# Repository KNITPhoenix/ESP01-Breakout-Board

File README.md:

# ESP01-Breakout-Board
ESP01 is a module that comes along with ESP8266 and an SPI flash memory but its not breadboard friendly. So in order to program and use it in, we use a breakout development board. This is a simple breakout board that gives the capabilities to program it and use its code simultaneously without much changes.

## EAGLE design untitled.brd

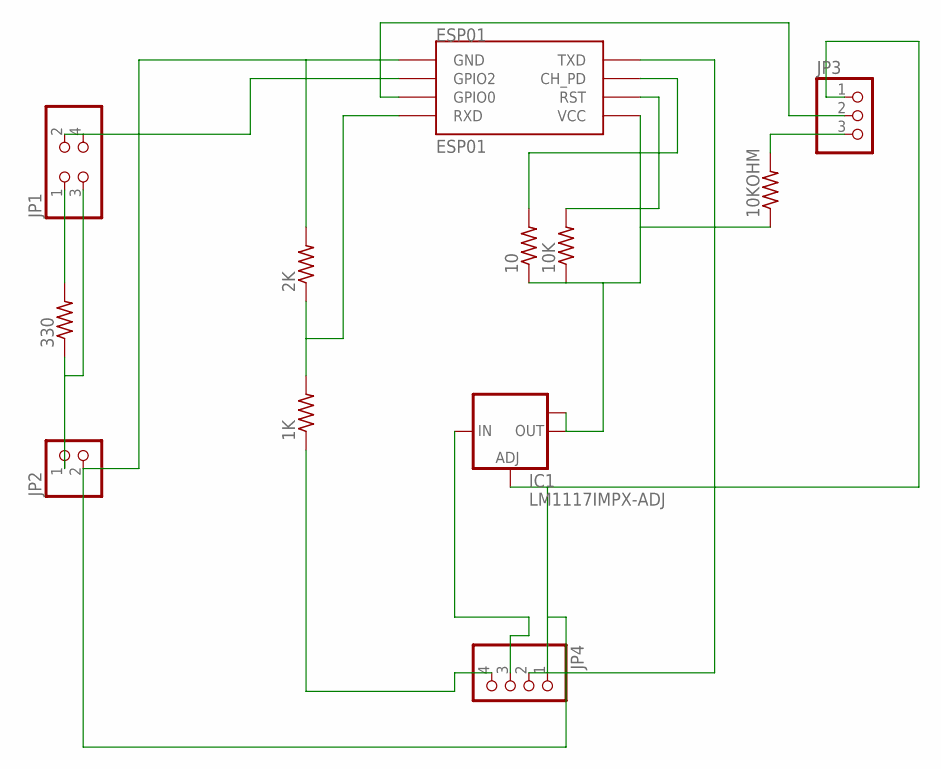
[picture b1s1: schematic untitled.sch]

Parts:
1K, 2K, 10, 10K, 10KOHM, 330: R-US_0204/7; 0204/7
ESP01: ESP01
IC1: LM1117IMPX-ADJ; SOT223
JP1: PINHD-2X2; 2X02
JP2: PINHD-1X2; 1X02
JP3: PINHD-1X3; 1X03
JP4: PINHD-1X4; 1X04

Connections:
unnamed: 330.2, JP1.1
unnamed: 330.1, JP1.3, JP2.1
unnamed: 1K.2, 2K.1, ESP01.RX (RXD)
unnamed: 10.1, 10K.1, 10KOHM.1, ESP01.VCC, IC1.2 (OUT), IC1.TAB (OUT1)
unnamed: 1K.1, JP4.4
unnamed: ESP01.GPIO2, JP1.2, JP1.4
unnamed: 10.2, ESP01.CH_PD
unnamed: 10K.2, ESP01.RST
unnamed: IC1.3 (IN), JP4.3
unnamed: 2K.2, ESP01.GND, IC1.1 (ADJ), JP2.2, JP3.1, JP4.1
unnamed: ESP01.TX (TXD), JP4.2
unnamed: ESP01.GPIO0, JP3.2
unnamed: 10KOHM.2, JP3.3

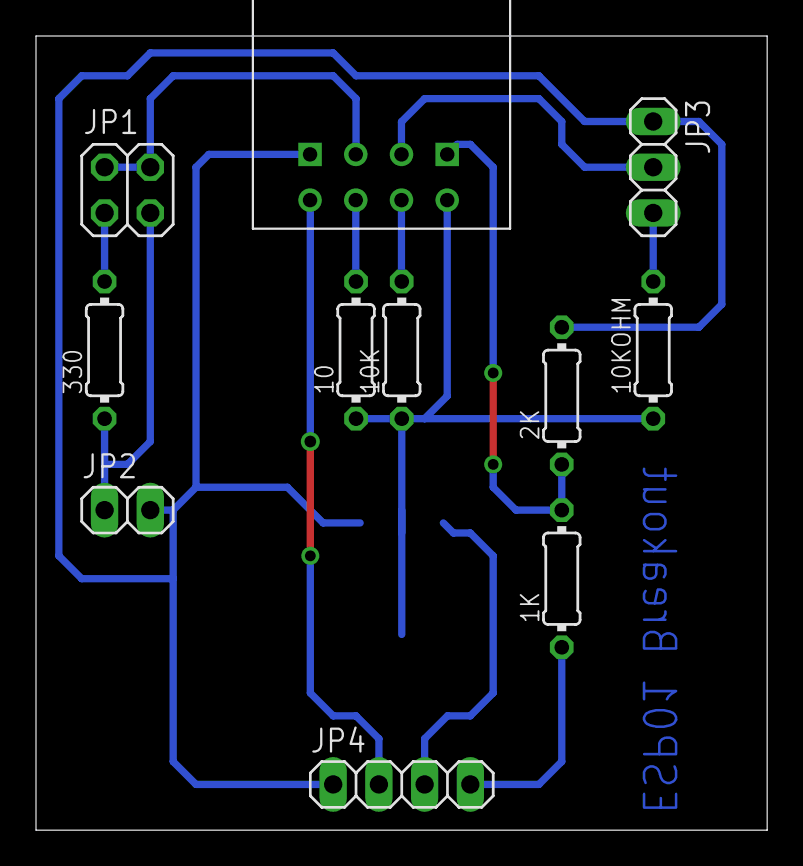
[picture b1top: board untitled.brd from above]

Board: 2 copper layers, 40.6 x 44.1 mm, 12 parts (1 on the bottom side), 13 nets.
